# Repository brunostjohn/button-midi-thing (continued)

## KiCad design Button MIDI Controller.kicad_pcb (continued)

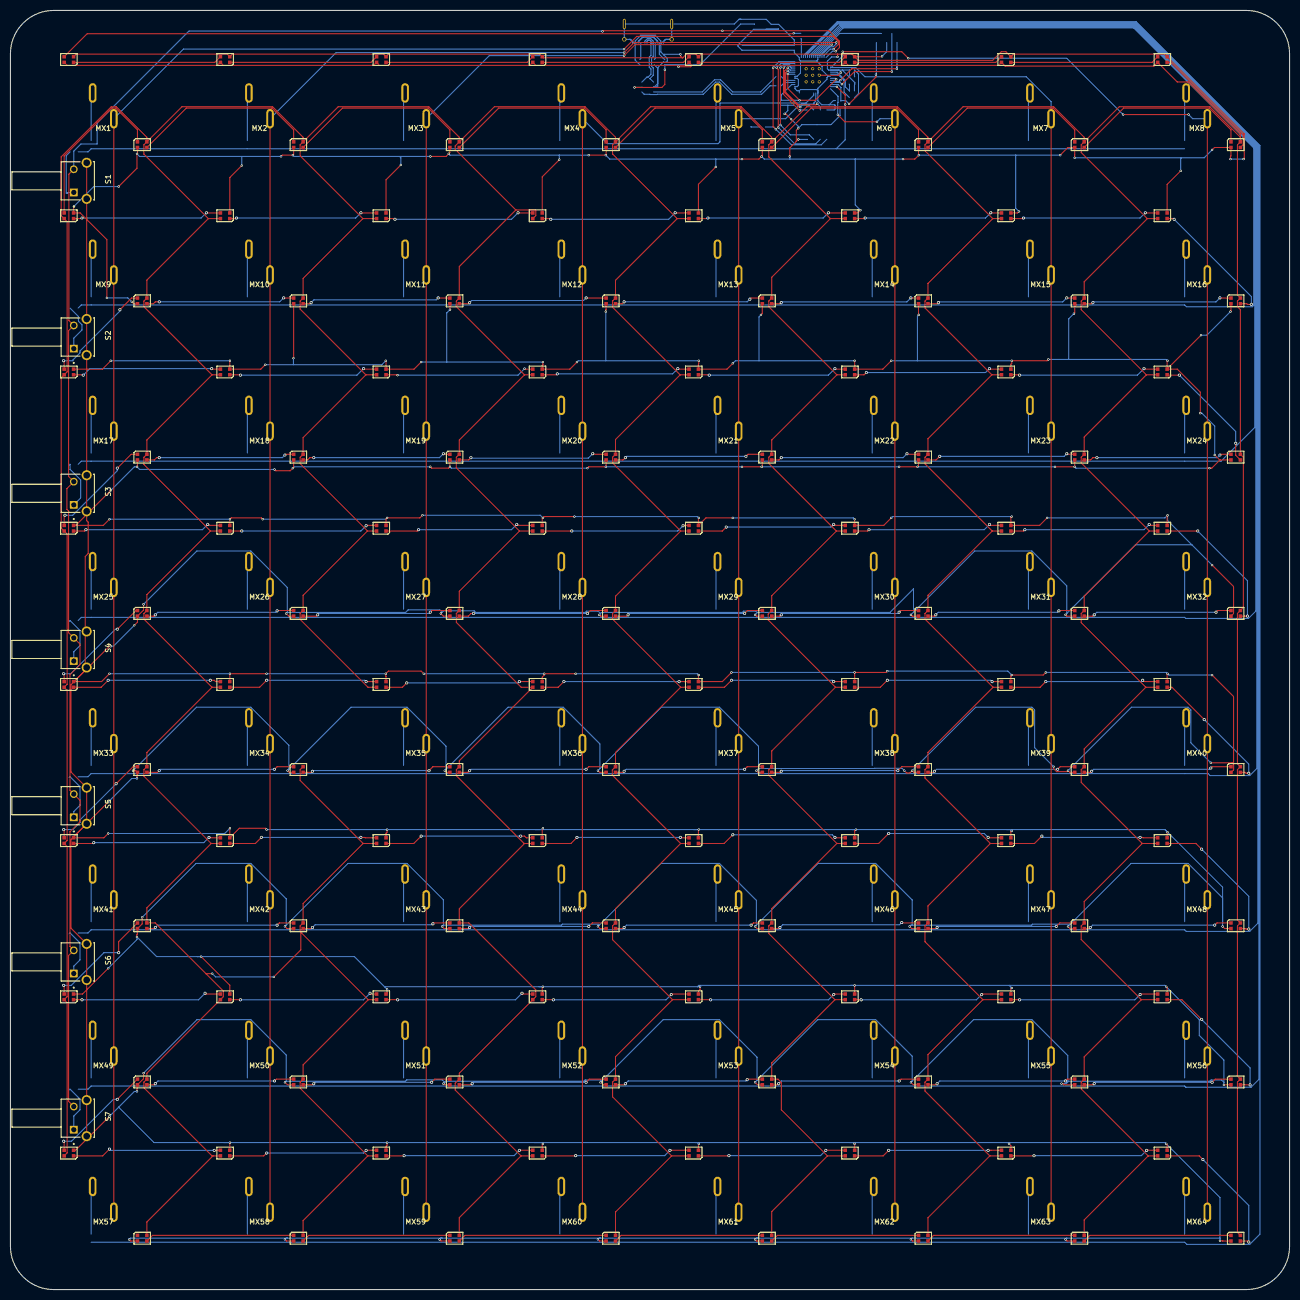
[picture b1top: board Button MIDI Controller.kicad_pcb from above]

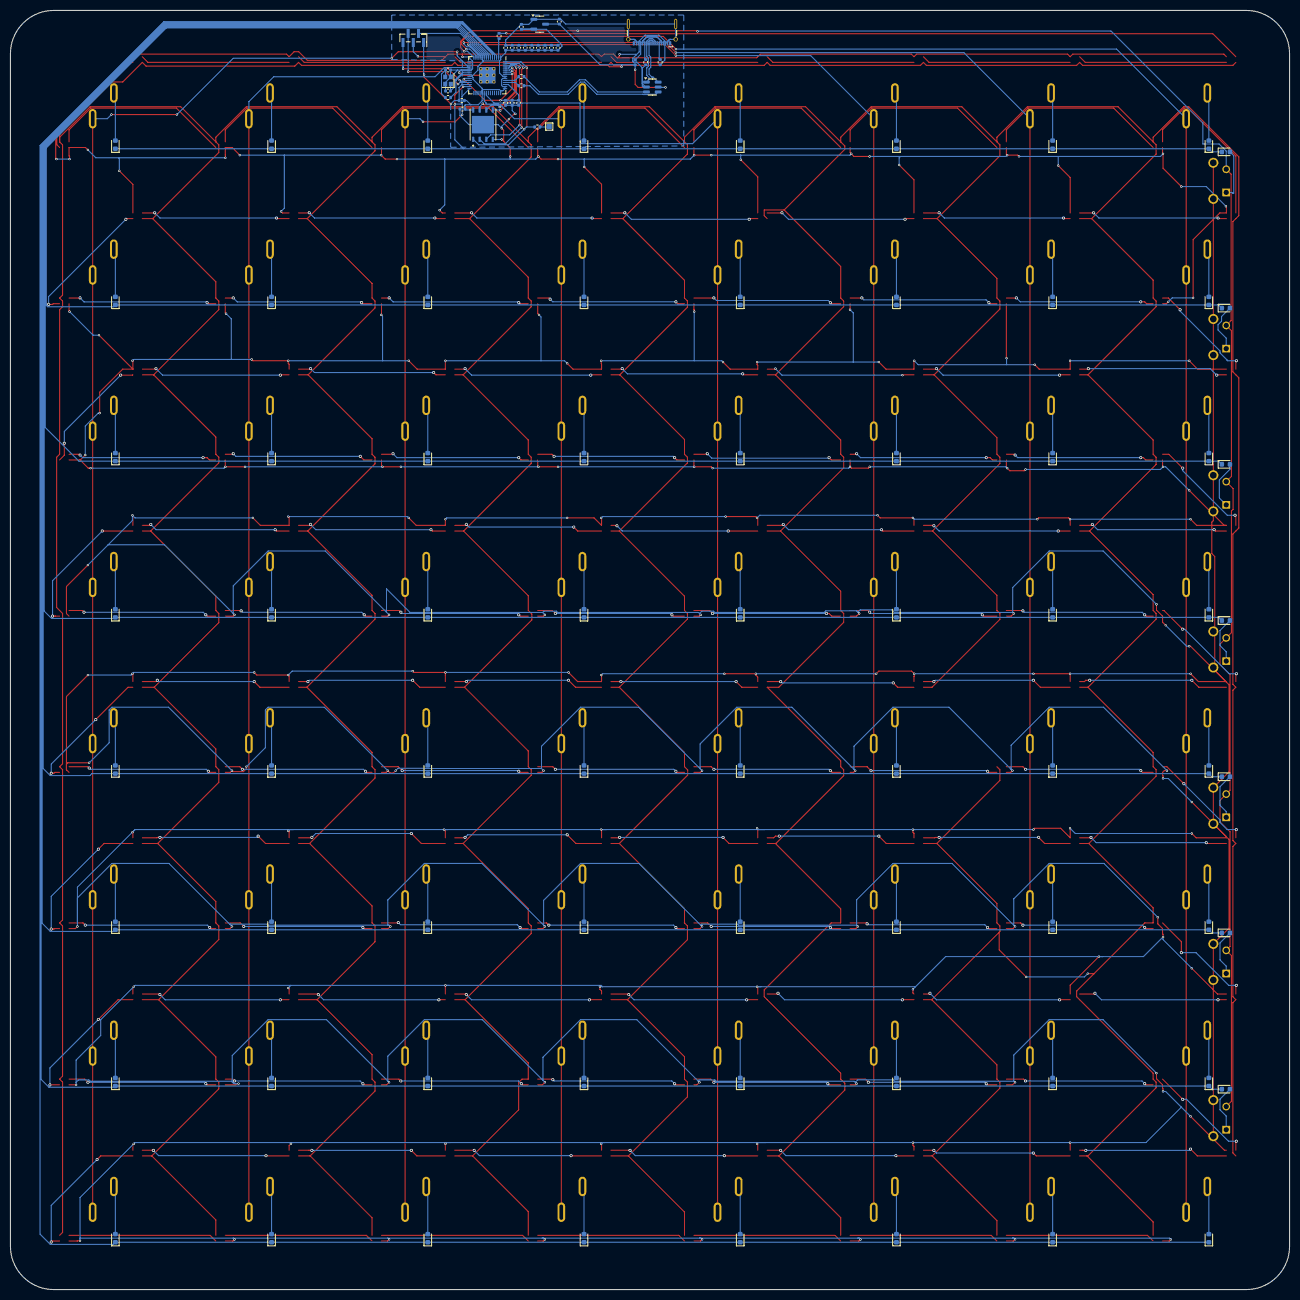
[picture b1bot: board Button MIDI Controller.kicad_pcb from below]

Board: 2 copper layers, 248.1 x 248.1 mm, 304 parts (105 on the bottom side), 243 nets.

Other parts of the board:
D193, D194, D195, D196, D197, D198, D199: D_Small; D_0603_1608Metric-notxt
S1, S2, S3, S4, S5, S6, S7: TS11-674-120-BK-100-RA-D; SW_TS11-674-120-BK-100-RA-D

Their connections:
COL8: S1.2, S2.2, S3.2, S4.2, S5.2, S6.2, S7.2; also elsewhere on the board
GND: S1.3 (GND), S1.4 (GND), S2.3 (GND), S2.4 (GND), S3.3 (GND), S3.4 (GND), S4.3 (GND), S4.4 (GND), S5.3 (GND), S5.4 (GND), S6.3 (GND), S6.4 (GND), S7.3 (GND), S7.4 (GND); also elsewhere on the board
unnamed: D193.2 (A), S1.1
unnamed: D194.2 (A), S2.1
unnamed: D195.2 (A), S3.1
unnamed: D196.2 (A), S4.1
unnamed: D197.2 (A), S5.1
unnamed: D198.2 (A), S6.1
unnamed: D199.2 (A), S7.1
ROW0: D193.1 (K); also elsewhere on the board
ROW1: D194.1 (K); also elsewhere on the board
ROW2: D195.1 (K); also elsewhere on the board
ROW3: D196.1 (K); also elsewhere on the board
ROW4: D197.1 (K); also elsewhere on the board
ROW5: D198.1 (K); also elsewhere on the board
ROW6: D199.1 (K); also elsewhere on the board

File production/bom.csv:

Designator,Footprint,Quantity,Value,LCSC Part #
"C1, C2",0402,2,22 pF,C541361
"C10, C11, C12, C13, C14, C15, C3, C7, C8, C9",0402,10,100nF,C541407
"C16, C4, C5, C6",0402,4,1uF,C437522
C17,0402,1,10uF,C6119763
"D1, D10, D11, D12, D13, D14, D15, D16, D17, D18, D19, D193, D194, D195, D196, D197, D198, D199, D2, D20, D21, D22, D23, D24, D25, D26, D27, D28, D29, D3, D30, D31, D32, D33, D34, D35, D36, D37, D38, D39, D4, D40, D41, D42, D43, D44, D45, D46, D47, D48, D49, D5, D50, D51, D52, D53, D54, D55, D56, D57, D58, D59, D6, D60, D61, D62, D63, D64, D7, D8, D9",D_SOD-123-notxt,71,D_Small,C2099
"D100, D101, D102, D103, D104, D105, D106, D107, D108, D109, D110, D111, D112, D113, D114, D115, D116, D117, D118, D119, D120, D121, D122, D123, D124, D125, D126, D127, D128, D129, D130, D131, D132, D133, D134, D135, D136, D137, D138, D139, D140, D141, D142, D143, D144, D145, D146, D147, D148, D149, D150, D151, D152, D153, D154, D155, D156, D157, D158, D159, D160, D161, D162, D163, D164, D165, D166, D167, D168, D169, D170, D171, D172, D173, D174, D175, D176, D177, D178, D179, D180, D181, D182, D183, D184, D185, D186, D187, D188, D189, D190, D191, D192, D65, D66, D67, D68, D69, D70, D71, D72, D73, D74, D75, D76, D77, D78, D79, D80, D81, D82, D83, D84, D85, D86, D87, D88, D89, D90, D91, D92, D93, D94, D95, D96, D97, D98, D99",LED_WS2812B-2020_PLCC4_2.0x2.0mm-notext,128,WS2812B-2020,C965555
F1,0402,1,500mA,C136320
J2,USB_C_Receptacle_G-Switch_GT-USB-7025-notxt,1,USB_C_Receptacle_USB2.0_16P,C963213
"R1, R2, R5",0402,3,1k,C11702
"R3, R4",0402,2,27R,C25100
"R6, R7",0402,2,5k1,C25905
R8,0402,1,500R,C124084
U1,RP2040-QFN-56-notext,1,RP2040,C2040
U2,SON127P500X600X80-9N-notxt,1,W25Q16JVZPIQ,C377853
U3,SOT-23-6-notxt,1,USBLC6-2SC6,C7519
U4,SOT-23-3-notxt,1,XC6206PxxxMR,C5148692
Y1,Crystal_SMD_2016-4Pin_2.0x1.6mm-notxt,1,X322512MSB4SI,C9002

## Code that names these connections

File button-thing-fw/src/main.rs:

#![no_std]
#![no_main]

use anyhow::Context;
use board::init_usb_midi;
use cortex_m::delay::Delay;

use defmt::*;
use defmt_rtt as _;
use embedded_alloc::LlffHeap as Heap;

use globals::USB_MIDI;
use heapless::Vec;

use midi_convert::midi_types::MidiMessage;
use midi_convert::parse::MidiTryParseSlice;

use panic_probe as _;

use rp2040_hal::clocks::init_clocks_and_plls;
use rp2040_hal::gpio::{PinState, Pins};
use rp2040_hal::pac::interrupt;
use rp2040_hal::pio::PIOExt;
use rp2040_hal::{entry, Clock, Sio, Timer, Watchdog};
use smart_leds::{brightness, SmartLedsWrite, RGB8};
use usb_device::UsbError;
use usbd_midi::{CableNumber, UsbMidiEventPacket, UsbMidiPacketReader};
use ws2812_pio::Ws2812;

use crate::matrix::Matrix;
use crate::usb::{handle_midi_packets, poll_usb_midi, send_midi_message};

mod board;
mod colour;
mod globals;
mod matrix;
mod usb;

const SYSEX_BUFFER_SIZE: usize = 64;

fn main() -> anyhow::Result<()> {
    info!("Started firmware!");

    let mut pac = rp2040_hal::pac::Peripherals::take().context("Failed to take peripherals")?;
    let core =
        rp2040_hal::pac::CorePeripherals::take().context("Failed to take core peripherals")?;
    let mut watchdog = Watchdog::new(pac.WATCHDOG);
    let sio = Sio::new(pac.SIO);

    let external_xtal_freq_hz = 12_000_000u32;
    let clocks = init_clocks_and_plls(
        external_xtal_freq_hz,
        pac.XOSC,
        pac.CLOCKS,
        pac.PLL_SYS,
        pac.PLL_USB,
        &mut pac.RESETS,
        &mut watchdog,
    )
    .map_err(|e| anyhow::anyhow!("Failed to initialize clocks: {:?}", e))
    .context("Failed to initialize clocks!")?;
    let timer = Timer::new(pac.TIMER, &mut pac.RESETS, &clocks);

    init_usb_midi(
        pac.USBCTRL_REGS,
        pac.USBCTRL_DPRAM,
        clocks.usb_clock,
        &mut pac.RESETS,
    )
    .context("Failed to initialize USB MIDI")?;

    let pins = Pins::new(
        pac.IO_BANK0,
        pac.PADS_BANK0,
        sio.gpio_bank0,
        &mut pac.RESETS,
    );

    let (mut pio, sm0, _, _, _) = pac.PIO0.split(&mut pac.RESETS);

    // let mut ws = Ws2812::new(
    //     pins.gpio15.into_function(),
    //     &mut pio,
    //     sm0,
    //     clocks.peripheral_clock.freq(),
    //     timer.count_down(),
    // );

    let mut delay = Delay::new(core.SYST, clocks.system_clock.freq().to_Hz());

    let mut sysex_receive_buffer = Vec::<u8, SYSEX_BUFFER_SIZE>::new();

    let mut matrix = Matrix::new(
        [
            pins.gpio3.into_pull_up_input().into_dyn_pin(),
            pins.gpio5.into_pull_up_input().into_dyn_pin(),
            pins.gpio11.into_pull_up_input().into_dyn_pin(),
            pins.gpio6.into_pull_up_input().into_dyn_pin(),
            pins.gpio7.into_pull_up_input().into_dyn_pin(),
            pins.gpio8.into_pull_up_input().into_dyn_pin(),
            pins.gpio9.into_pull_up_input().into_dyn_pin(),
            pins.gpio10.into_pull_up_input().into_dyn_pin(),
        ],
        [
            pins.gpio22
                .into_push_pull_output_in_state(PinState::Low)
                .into_dyn_pin(),
            pins.gpio23
                .into_push_pull_output_in_state(PinState::Low)
                .into_dyn_pin(),
            pins.gpio24
                .into_push_pull_output_in_state(PinState::Low)
                .into_dyn_pin(),
            pins.gpio25
                .into_push_pull_output_in_state(PinState::Low)
                .into_dyn_pin(),
            pins.gpio29
                .into_push_pull_output_in_state(PinState::Low)
                .into_dyn_pin(),
            pins.gpio28
                .into_push_pull_output_in_state(PinState::Low)
                .into_dyn_pin(),
            pins.gpio27
                .into_push_pull_output_in_state(PinState::Low)
                .into_dyn_pin(),
            pins.gpio26
                .into_push_pull_output_in_state(PinState::Low)
                .into_dyn_pin(),
        ],
        &mut delay,
    );

    loop {
        print_if_err(|| {
            handle_midi(&mut sysex_receive_buffer)?;
            emit_changed_notes(&mut matrix)?;

            Ok(())
        });
    }
}

fn print_if_err<F>(mut f: F)
where
    F: FnMut() -> anyhow::Result<()>,
{
    let res = f();
    if let Err(e) = res {
        error!("Failed to run function");
    }
}

fn emit_changed_notes(matrix: &mut Matrix<'_>) -> anyhow::Result<()> {
    let notes = matrix.render_notes()?;

    for changed_note in notes.as_ref().iter().flatten() {
        if let Err(e) = send_midi_message(*changed_note) {
            // find way to print
            error!("Failed to send MIDI message!");
        }
    }

    Ok(())
}

fn handle_midi(sysex_receive_buffer: &mut Vec<u8, SYSEX_BUFFER_SIZE>) -> anyhow::Result<()> {
    if !poll_usb_midi()? {
        return Ok(());
    }

    handle_midi_packets(
        |message| match message {
            _ => Ok(()),
        },
        sysex_receive_buffer,
    )
}

#[allow(non_snake_case)]
#[interrupt]
unsafe fn USBCTRL_IRQ() {
    critical_section::with(|_| {
        poll_usb_midi().expect("USB and MIDI should be initialized");
    });
}

#[global_allocator]
static HEAP: Heap = Heap::empty();

#[entry]
fn entry() -> ! {
    {
        use core::mem::MaybeUninit;
        const HEAP_SIZE: usize = 1024;
        static mut HEAP_MEM: [MaybeUninit<u8>; HEAP_SIZE] = [MaybeUninit::uninit(); HEAP_SIZE];
        unsafe { HEAP.init(&raw mut HEAP_MEM as usize, HEAP_SIZE) }
    }
    info!("Heap initialized");

    if let Err(e) = main() {
        error!("A FATAL ERROR HAS OCCURRED AND EXECUTION CANNOT CONTINUE!");
        // print the damn thing
    }

    loop {}
}

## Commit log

2025-05-18 initialise
2025-05-22 pluh
2025-05-30 updatres again
2025-05-30 add zefir to da mix
2025-05-31 update shit
2025-05-31 move gerbers
2025-05-31 yeah have some updates my g
2025-05-31 made minor changes
2025-05-31 init project
2025-05-31 boardstar updates & me ruining it
2025-05-31 im done for the day with the f/w
2025-06-01 readme and other updates
2025-06-01 lfs time
2025-06-02 some modifications i forgor
2025-06-08 matrix scanning early untested impl
2025-06-09 reroute usb, crystal, usblc
